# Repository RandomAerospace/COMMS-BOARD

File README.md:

Comms board with APRS GNSS
V1 has been flight tested, V2 has fixed existing issues under issues tab
Accompanying firmware: https://github.com/RandomAerospace/BEAR13_FIRMWARE
Summary of the project, presented at SARTS: https://www.sarts.org.sg/presentations-quarterly-meeting-may-2026/

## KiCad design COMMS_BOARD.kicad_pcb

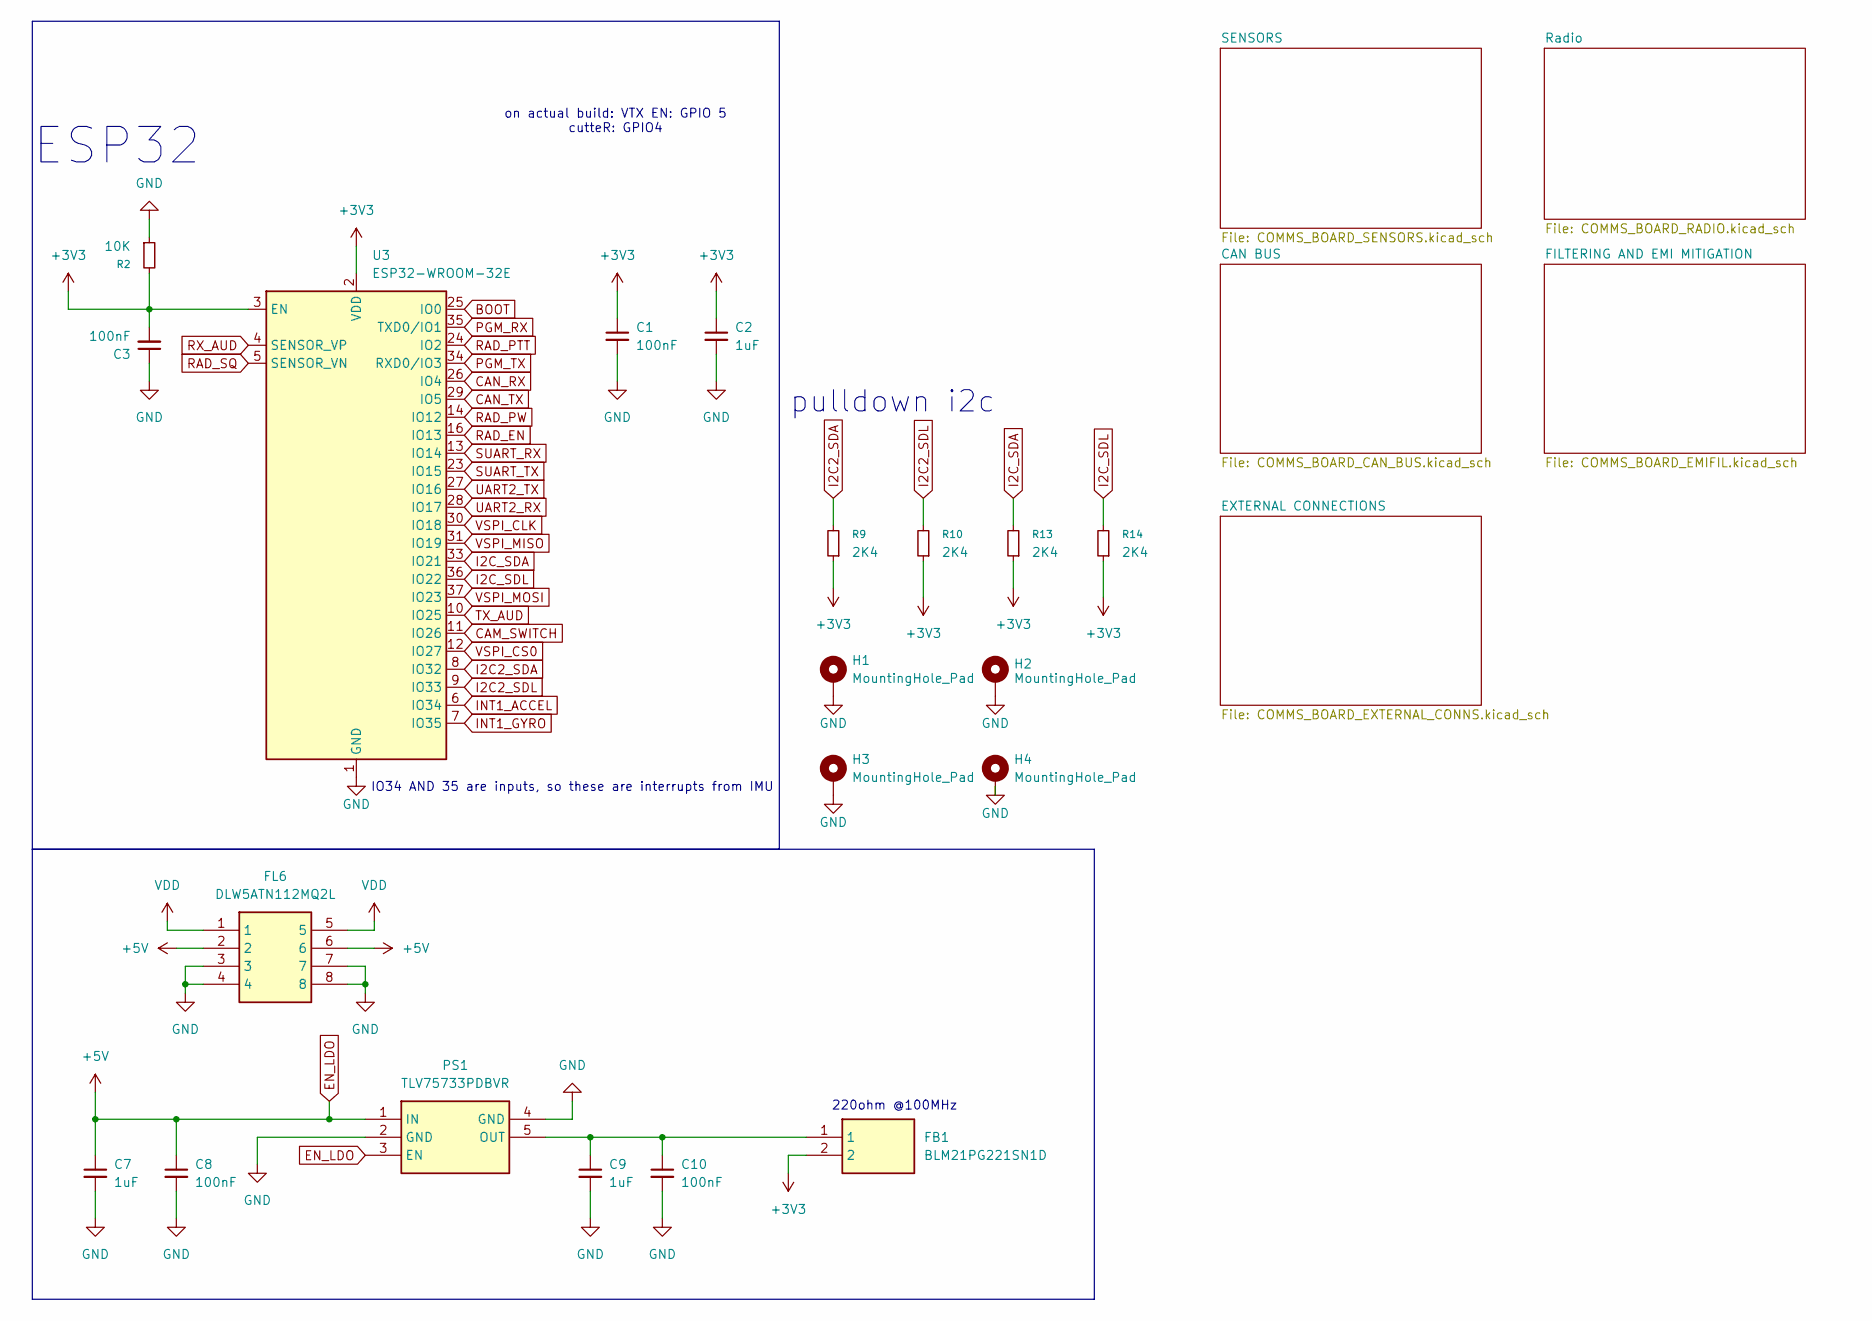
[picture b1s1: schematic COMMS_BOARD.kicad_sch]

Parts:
C1, C3, C8, C10: 100nF; C_0603_1608Metric
C2, C7, C9: 1uF; C_0603_1608Metric
FB1: BLM21PG221SN1D; BEADC2012X105N; Mouser Part Number 81-BLM21P221SG
FL6: DLW5ATN112MQ2L; DLW5BSN302SQ2L; Mouser Part Number 81-DLW5ATN112MQ2L
H1, H2, H3, H4: MountingHole_Pad; MountingHole_2.2mm_M2_ISO7380_Pad
PS1: TLV75733PDBVR; SOT95P280X145-5N; Mouser Part Number 595-TLV75733PDBVR
R2: 10K; R_0603_1608Metric
R9, R10, R13, R14: 2K4; R_0603_1608Metric
U3: ESP32-WROOM-32E; ESP32-WROOM-32D

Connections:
+3V3: C1.1, C2.1, C3.2, FB1.2, R2.2, R9.1, R10.1, R13.1, R14.1, U3.2 (VDD), U3.3 (EN); also elsewhere on the board
BOOT: U3.25 (IO0); also elsewhere on the board
CAM_SWITCH: U3.11 (IO26); also elsewhere on the board
CAN_RX: U3.26 (IO4); also elsewhere on the board
CAN_TX: U3.29 (IO5); also elsewhere on the board
EN_LDO: C7.1, C8.1, FL6.2, FL6.6, PS1.1 (IN), PS1.3 (EN); also elsewhere on the board
GND: C1.2, C2.2, C3.1, C7.2, C8.2, C9.2, C10.2, FL6.3, FL6.4, FL6.7, FL6.8, H1.1 (1_1), H2.1 (1_1), H3.1 (1_1), H4.1 (1_1), PS1.2 (GND), PS1.4 (GND), R2.1, U3.1 (GND), U3.15 (GND), U3.38 (GND), U3.39 (GND); also elsewhere on the board
I2C2_SDA: R9.2, U3.8 (IO32); also elsewhere on the board
I2C2_SDL: R10.2, U3.9 (IO33); also elsewhere on the board
I2C_SDA: R13.2, U3.33 (IO21); also elsewhere on the board
I2C_SDL: R14.2, U3.36 (IO22); also elsewhere on the board
INT1_ACCEL: U3.6 (IO34); also elsewhere on the board
INT1_GYRO: U3.7 (IO35); also elsewhere on the board
unnamed: FL6.1, FL6.5
unnamed: C9.1, C10.1, FB1.1, PS1.5 (OUT)
PGM_RX: U3.35 (TXD0/IO1); also elsewhere on the board
PGM_TX: U3.34 (RXD0/IO3); also elsewhere on the board
RAD_EN: U3.16 (IO13); also elsewhere on the board
RAD_PTT: U3.24 (IO2); also elsewhere on the board
RAD_PW: U3.14 (IO12); also elsewhere on the board
RAD_SQ: U3.5 (SENSOR_VN); also elsewhere on the board
RX_AUD: U3.4 (SENSOR_VP); also elsewhere on the board
SUART_RX: U3.13 (IO14); also elsewhere on the board
SUART_TX: U3.23 (IO15); also elsewhere on the board
TX_AUD: U3.10 (IO25); also elsewhere on the board
UART2_RX: U3.28 (IO17); also elsewhere on the board
UART2_TX: U3.27 (IO16); also elsewhere on the board
VSPI_CLK: U3.30 (IO18); also elsewhere on the board
VSPI_CS0: U3.12 (IO27); also elsewhere on the board
VSPI_MISO: U3.31 (IO19); also elsewhere on the board
VSPI_MOSI: U3.37 (IO23)

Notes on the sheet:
pulldown i2c
ESP32
IO34 AND 35 are inputs, so these are interrupts from IMU
220ohm @100MHz
on actual build: VTX EN: GPIO 5 cutteR: GPIO4

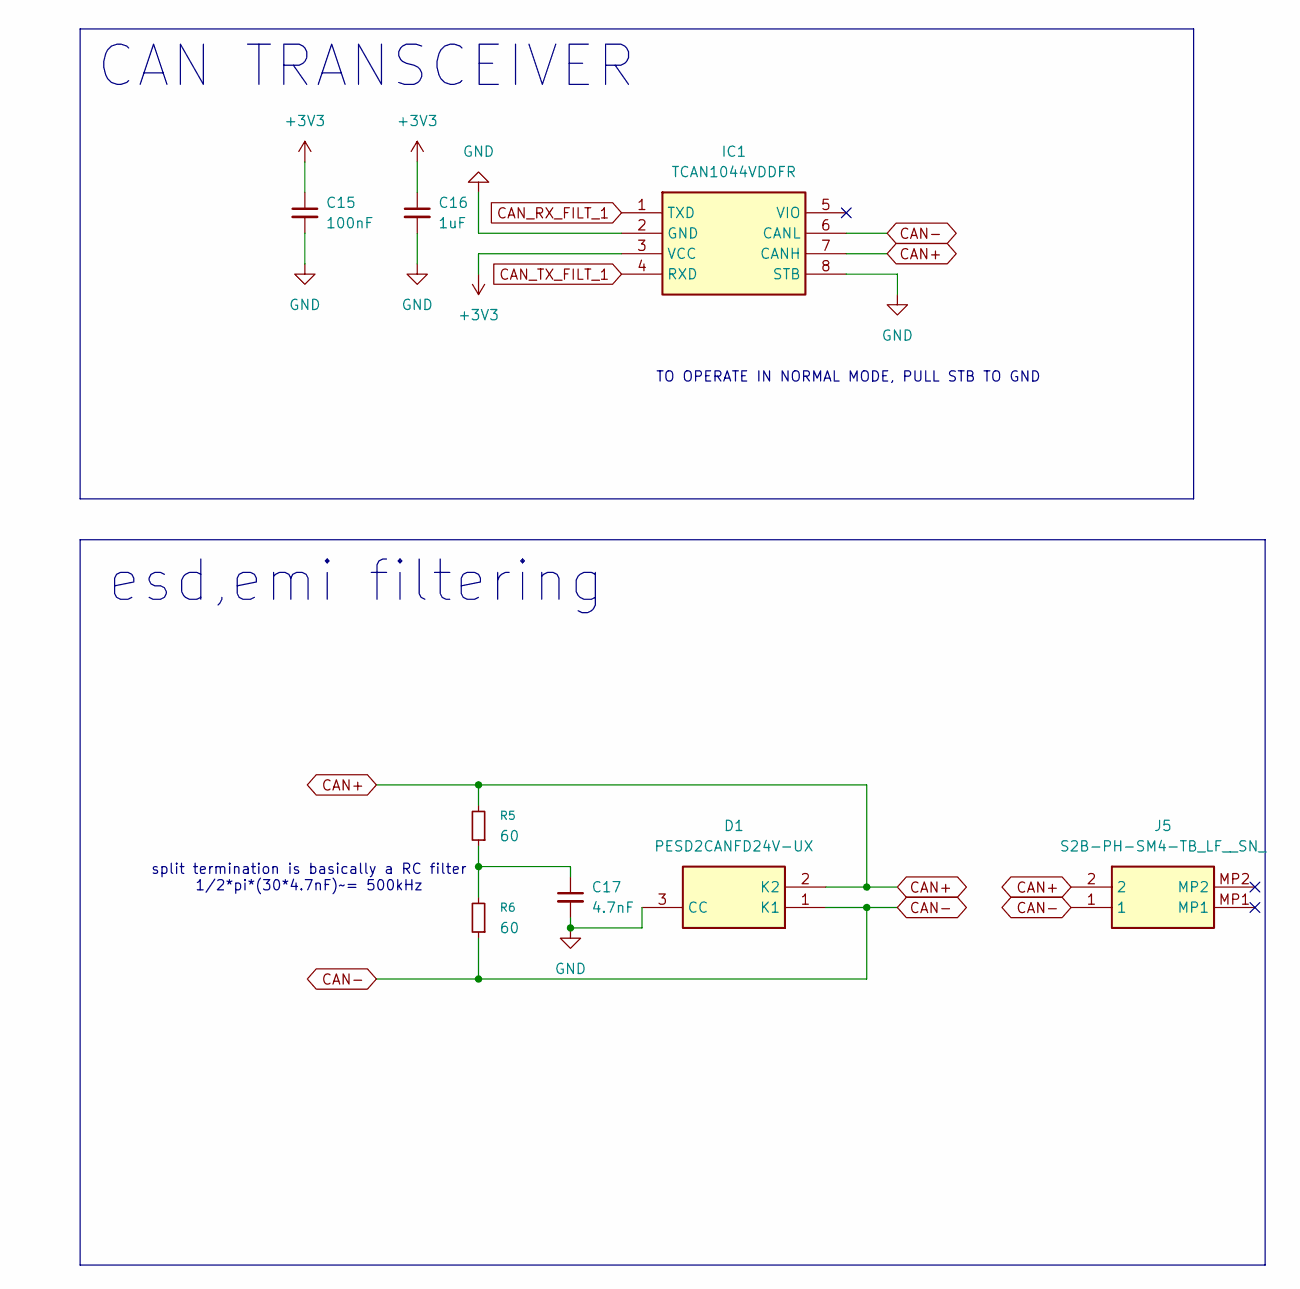
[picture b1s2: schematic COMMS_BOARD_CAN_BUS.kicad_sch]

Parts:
C15: 100nF; C_0603_1608Metric
C16: 1uF; C_0603_1608Metric
C17: 4.7nF; C_0603_1608Metric
D1: PESD2CANFD24V-UX; SOT65P210X110-3N; Mouser Part Number 771-PESD2CANFD24V-UX
IC1: TCAN1044VDDFR; SOT65P280X110-8N; Mouser Part Number 595-TCAN1044VDDFR
J5: S2B-PH-SM4-TB_LF__SN_; S2BPHSM4TBLFSN; Mouser Part Number N/A
R5, R6: 60; R_0603_1608Metric

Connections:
+3V3: C15.1, C16.1, IC1.3 (VCC); also elsewhere on the board
CAN+: D1.2 (K2), IC1.7 (CANH), J5.2, R5.2
CAN-: D1.1 (K1), IC1.6 (CANL), J5.1, R6.1
CAN_RX_FILT_1: IC1.1 (TXD); also elsewhere on the board
CAN_TX_FILT_1: IC1.4 (RXD); also elsewhere on the board
GND: C15.2, C16.2, C17.2, D1.3 (CC), IC1.2 (GND), IC1.8 (STB); also elsewhere on the board
unnamed: C17.1, R5.1, R6.2

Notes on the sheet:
split termination is basically a RC filter 1/2*pi*(30*4.7nF)~= 500kHz
esd,emi filtering
TO OPERATE IN NORMAL MODE, PULL STB TO GND
CAN TRANSCEIVER

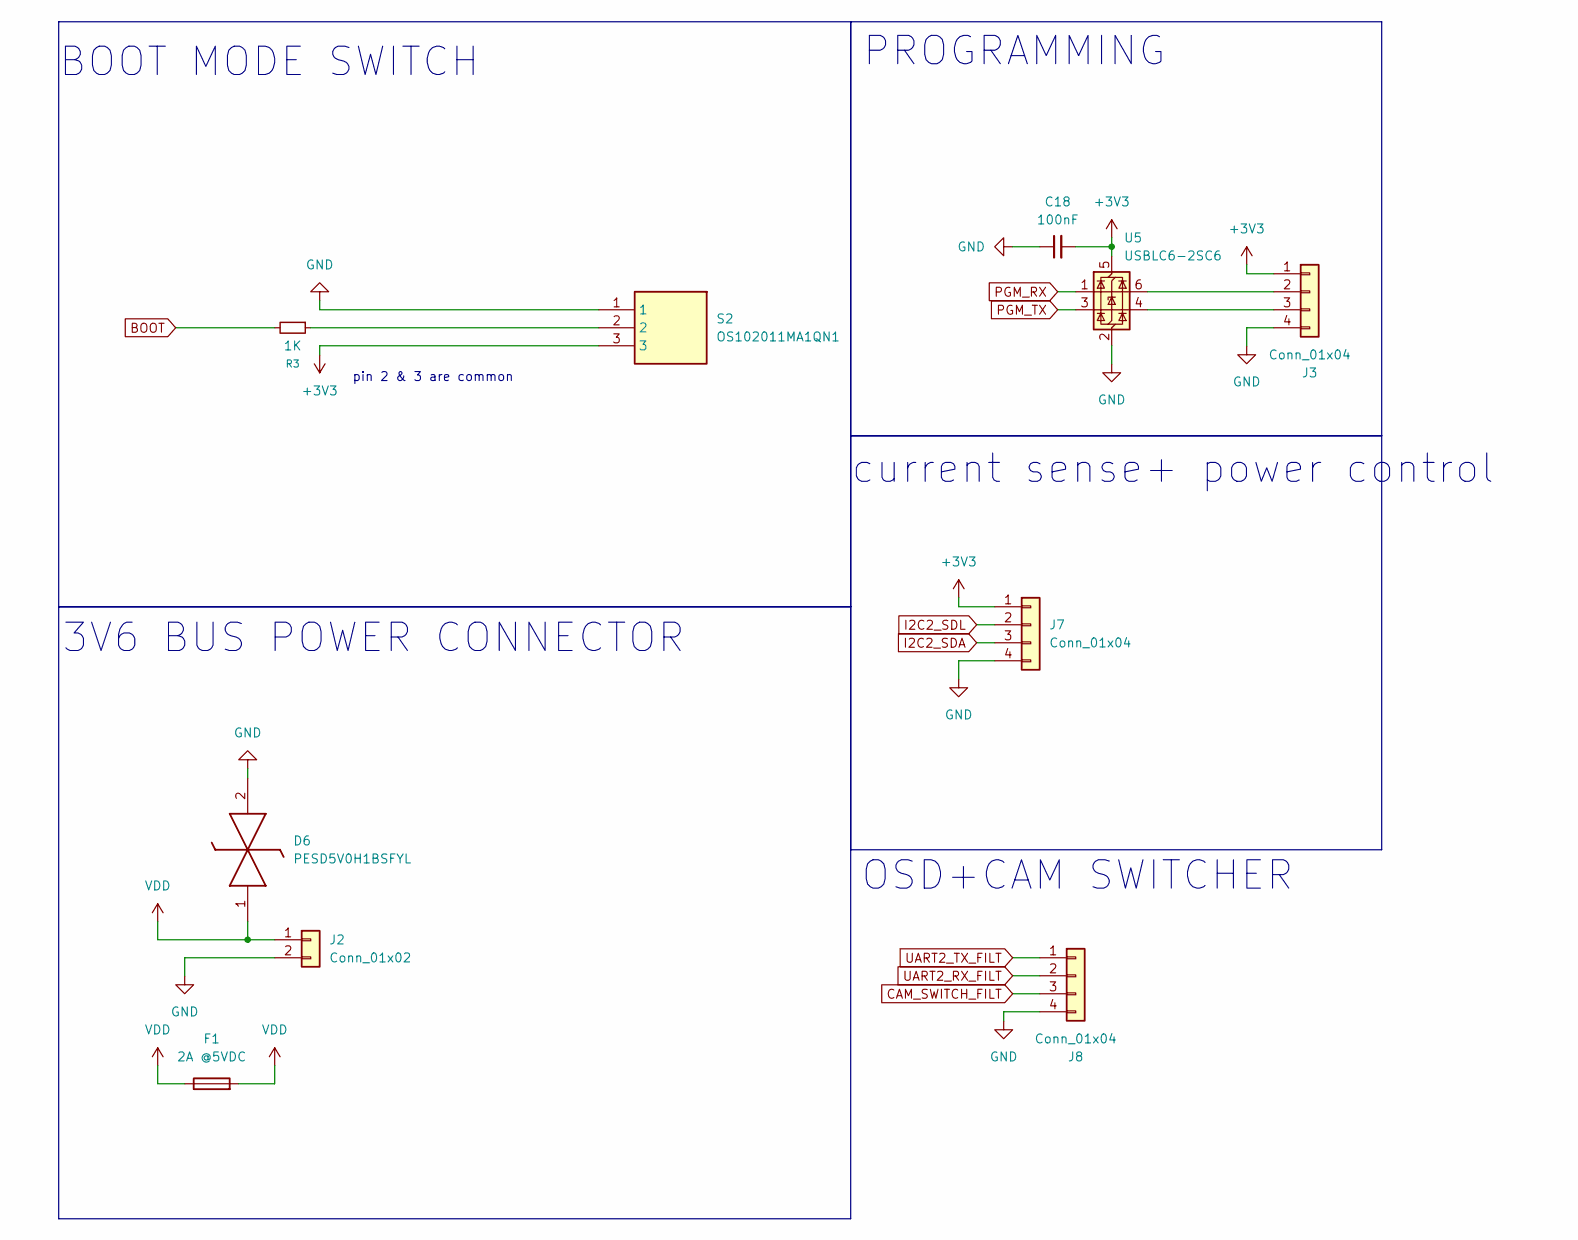
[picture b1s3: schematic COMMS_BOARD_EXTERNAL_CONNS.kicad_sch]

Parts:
C18: 100nF; C_0603_1608Metric
D6: PESD5V0H1BSFYL; PMEG3005AESFYL; Mouser Part Number 771-PESD5V0H1BSFYL
F1: 2A @5VDC; Fuse_0805_2012Metric
J2: Conn_01x02; JST_XH_S2B-XH-A-1_1x02_P2.50mm_Horizontal
J3, J8: Conn_01x04; JST_PH_B4B-PH-K_1x04_P2.00mm_Vertical
J7: Conn_01x04; JST_PH_S4B-PH-K_1x04_P2.00mm_Horizontal
R3: 1K; R_0603_1608Metric
S2: OS102011MA1QN1; Mouser Part Number 611-OS102011MA1QN1
U5: USBLC6-2SC6; SOT-23-6

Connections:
+3V3: C18.2, J3.1, J7.1, S2.3, U5.5 (VBUS); also elsewhere on the board
BOOT: R3.2; also elsewhere on the board
CAM_SWITCH_FILT: J8.3; also elsewhere on the board
GND: C18.1, D6.2 (K2), J2.2, J3.4, J7.4, J8.4, S2.1, U5.2 (GND); also elsewhere on the board
I2C2_SDA: J7.3; also elsewhere on the board
I2C2_SDL: J7.2; also elsewhere on the board
unnamed: J3.2, U5.6 (I/O1)
unnamed: J3.3, U5.4 (I/O2)
unnamed: R3.1, S2.2
PGM_RX: U5.1 (I/O1); also elsewhere on the board
PGM_TX: U5.3 (I/O2); also elsewhere on the board
UART2_RX_FILT: J8.2; also elsewhere on the board
UART2_TX_FILT: J8.1; also elsewhere on the board
VDD: D6.1 (K1), F1.1, F1.2, J2.1; also elsewhere on the board

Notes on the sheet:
PROGRAMMING
current sense+ power control
pin 2 & 3 are common
OSD+CAM SWITCHER
3V6 BUS POWER CONNECTOR
BOOT MODE SWITCH

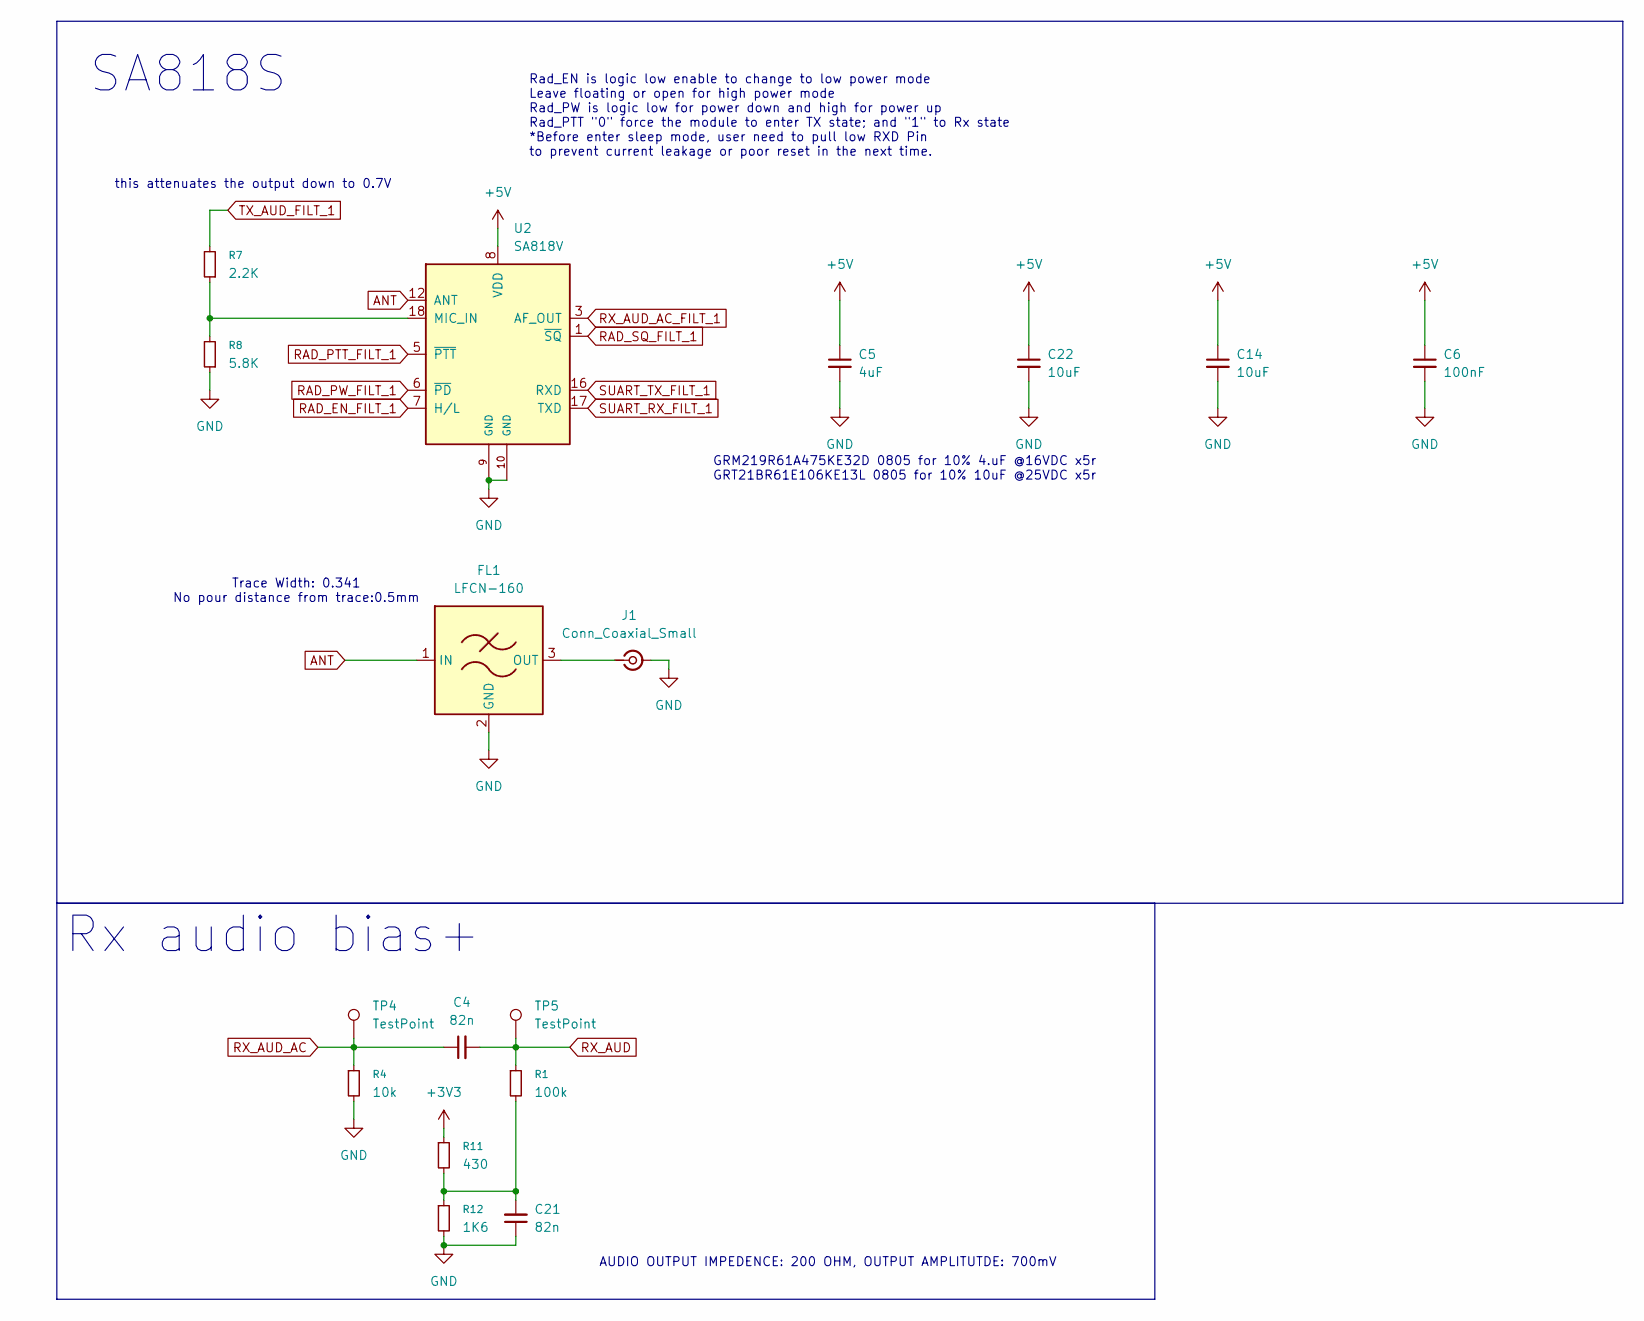
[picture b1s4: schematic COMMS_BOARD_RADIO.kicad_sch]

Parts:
C4, C21: 82n; C_0603_1608Metric
C5: 4uF; C_0805_2012Metric
C6: 100nF; C_0603_1608Metric
C14, C22: 10uF; C_0805_2012Metric
FL1: LFCN-160; Filter_Mini-Circuits_FV1206
J1: Conn_Coaxial_Small; MMCX_Molex_73415-1471_Vertical
R1: 100k; R_0603_1608Metric
R4: 10k; R_0603_1608Metric
R7: 2.2K; R_0603_1608Metric
R8: 5.8K; R_0603_1608Metric
R11: 430; R_0603_1608Metric
R12: 1K6; R_0603_1608Metric
TP4, TP5: TestPoint; TestPoint_Pad_D1.5mm
U2: SA818V; VHF_UHF_Module_generic

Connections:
+3V3: R11.1; also elsewhere on the board
ANT: FL1.1 (IN), U2.12 (ANT)
EN_LDO: C5.1, C6.1, C14.1, C22.1, U2.8 (VDD); also elsewhere on the board
GND: C5.2, C6.2, C14.2, C21.1, C22.2, FL1.2 (GND), FL1.4 (GND), J1.2 (Ext), R4.2, R8.1, R12.2, U2.9 (GND), U2.10 (GND); also elsewhere on the board
unnamed: C21.2, R1.2, R11.2, R12.1
unnamed: FL1.3 (OUT), J1.1 (In)
unnamed: R7.1, R8.2, U2.18 (MIC_IN)
RAD_EN_FILT_1: U2.7 (H/L); also elsewhere on the board
RAD_PTT_FILT_1: U2.5 (~PTT); also elsewhere on the board
RAD_PW_FILT_1: U2.6 (~PD); also elsewhere on the board
RAD_SQ_FILT_1: U2.1 (~SQ); also elsewhere on the board
RX_AUD: C4.2, R1.1, TP5.1 (1_1); also elsewhere on the board
RX_AUD_AC: C4.1, R4.1, TP4.1 (1_1); also elsewhere on the board
RX_AUD_AC_FILT_1: U2.3 (AF_OUT); also elsewhere on the board
SUART_RX_FILT_1: U2.17 (TXD); also elsewhere on the board
SUART_TX_FILT_1: U2.16 (RXD); also elsewhere on the board
TX_AUD_FILT_1: R7.2; also elsewhere on the board

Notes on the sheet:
SA818S
Trace Width: 0.341 No pour distance from trace:0.5mm
Rad_EN is logic low enable to change to low power mode Leave floating or open for high power mode Rad_PW is logic low for power down and high for power up Rad_PTT "0" force the module to enter TX state; and "1" to Rx state *Before enter sleep mode, user need to pull low RXD Pin to prevent current l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
this attenuates the output down to 0.7V
GRM219R61A475KE32D 0805 for 10% 4.uF @16VDC x5r GRT21BR61E106KE13L 0805 for 10% 10uF @25VDC x5r
Rx audio bias+
AUDIO OUTPUT IMPEDENCE: 200 OHM, OUTPUT AMPLITUTDE: 700mV

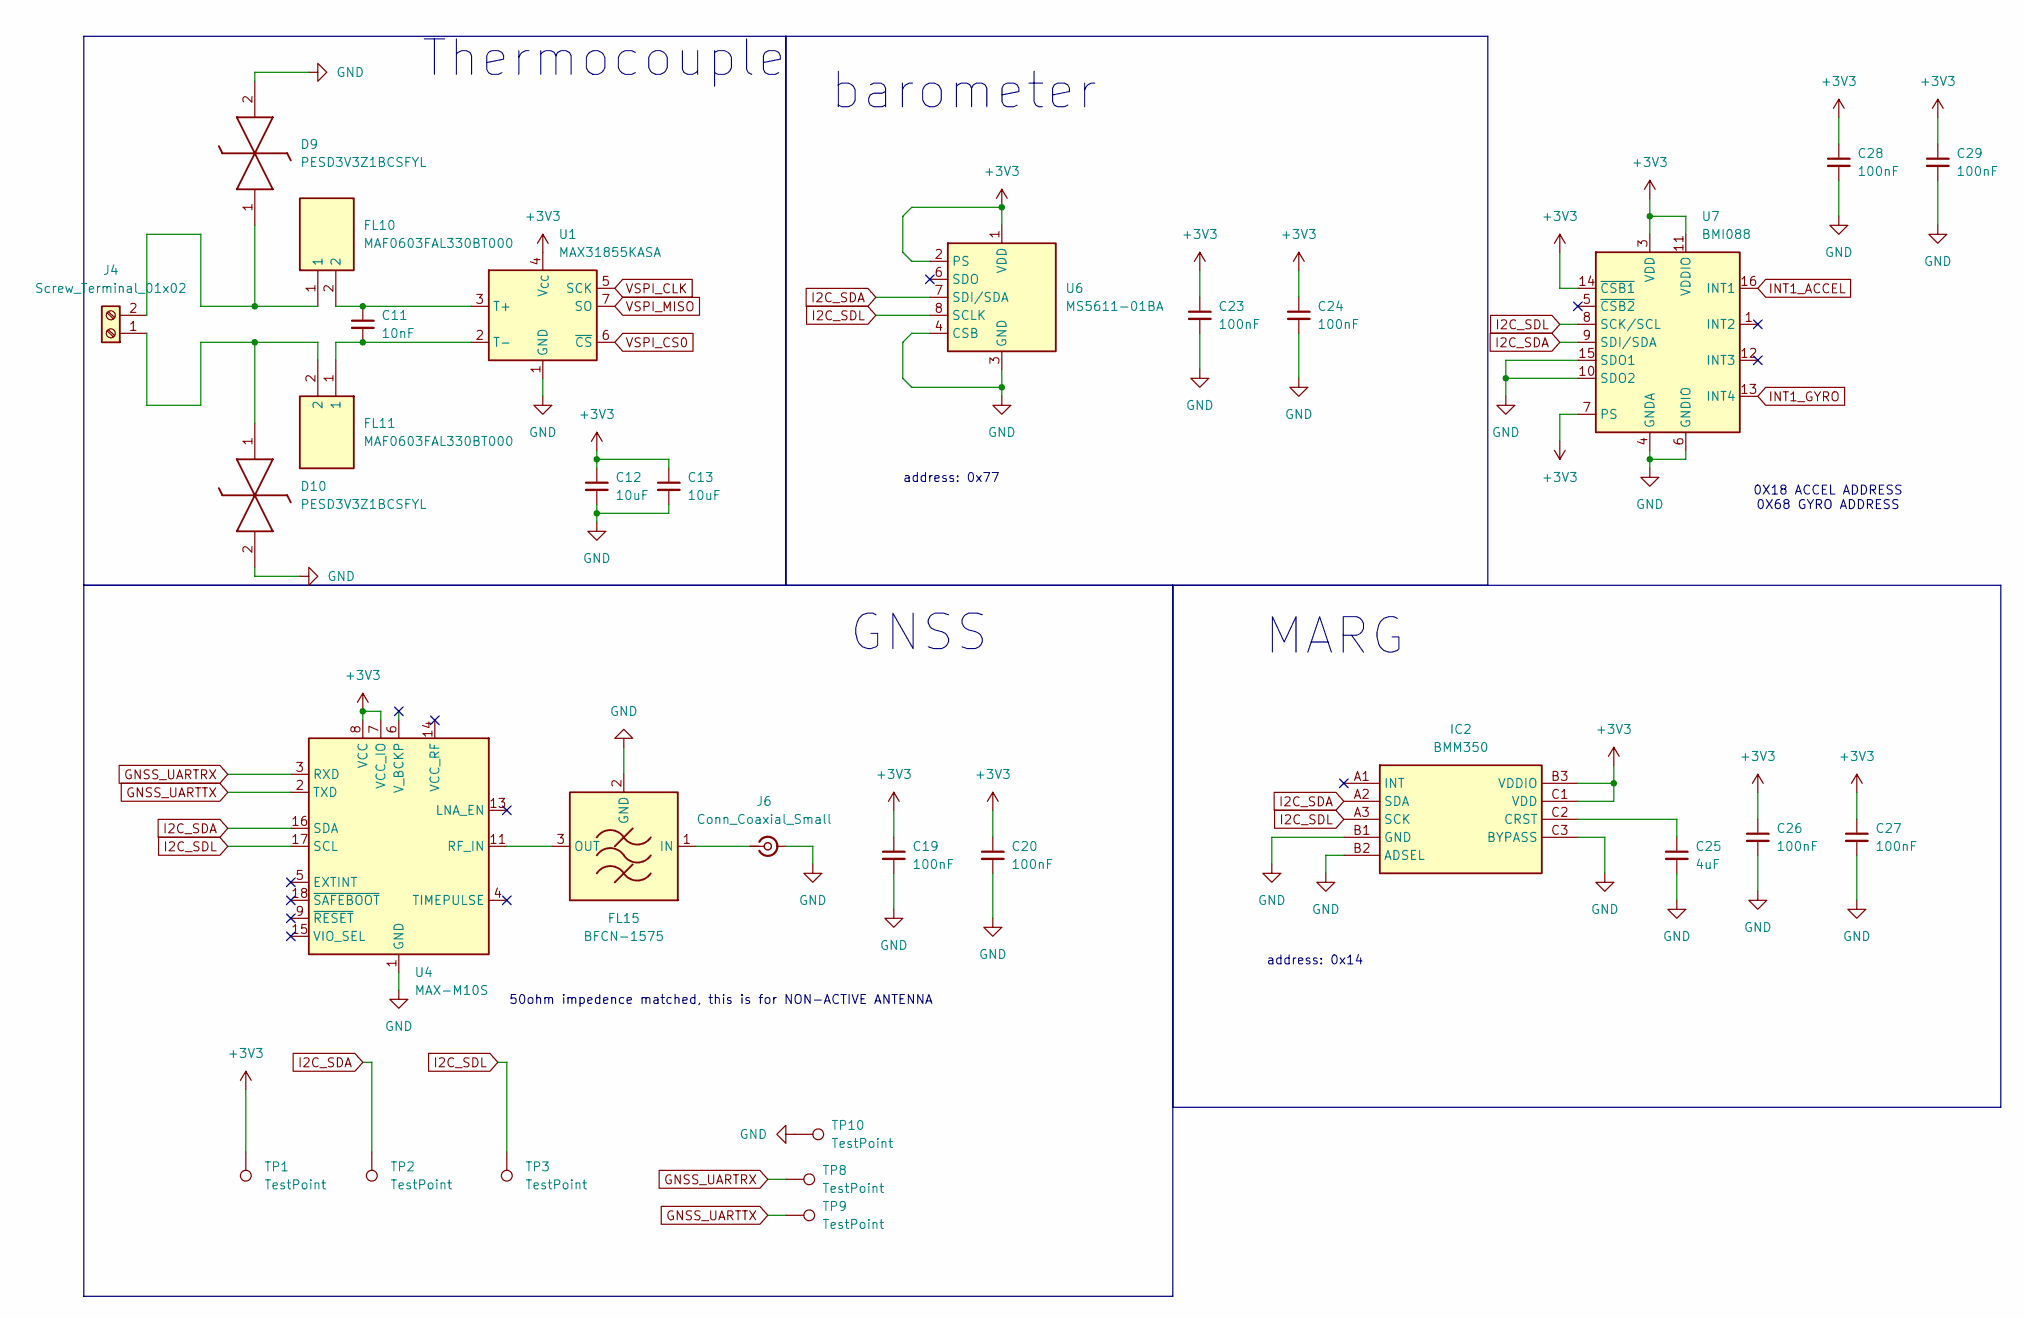
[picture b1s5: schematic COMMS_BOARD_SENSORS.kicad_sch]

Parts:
C11: 10nF; C_0603_1608Metric
C12, C13: 10uF; C_0603_1608Metric
C19, C20, C23, C24, C26, C27, C28, C29: 100nF; C_0603_1608Metric
C25: 4uF; C_0805_2012Metric
D9, D10: PESD3V3Z1BCSFYL; PMEG3005AESFYL; Mouser Part Number 771-PESD3V3Z1BCSFYL
FL10, FL11: MAF0603FAL330BT000; BEADC0603X33N; Mouser Part Number 810-MAF0603FAL330BT0
FL15: BFCN-1575; Filter_Mini-Circuits_FV1206
IC2: BMM350; BGA9C40P3X3_128X128X54; Mouser Part Number 262-BMM350
J4: Screw_Terminal_01x02; TerminalBlock_Xinya_XY308-2.54-2P_1x02_P2.54mm_Horizontal
J6: Conn_Coaxial_Small; U.FL_Hirose_U.FL-R-SMT-1_Vertical
TP1, TP2, TP3, TP8, TP9, TP10: TestPoint; TestPoint_Pad_D1.5mm
U1: MAX31855KASA; SOIC-8_3.9x4.9mm_P1.27mm
U4: MAX-M10S; ublox_MAX
U6: MS5611-01BA; LGA-8_3x5mm_P1.25mm
U7: BMI088; Bosch_LGA-16_4.5x3mm_P0.5mm_LayoutBorder7x1y_ClockwisePinNu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

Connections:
+3V3: C12.1, C13.1, C19.1, C20.1, C23.1, C24.1, C26.1, C27.1, C28.1, C29.1, IC2.B3 (VDDIO), IC2.C1 (VDD), TP1.1 (1_1), U1.4 (V_{CC}), U4.7 (VCC_IO), U4.8 (VCC), U6.1 (VDD), U6.2 (PS), U7.3 (VDD), U7.7 (PS), U7.11 (VDDIO), U7.14 (~CSB1); also elsewhere on the board
GND: C12.2, C13.2, C19.2, C20.2, C23.2, C24.2, C25.2, C26.2, C27.2, C28.2, C29.2, D9.2 (K2), D10.2 (K2), FL15.2 (GND), FL15.4 (GND), IC2.B1 (GND), IC2.B2 (ADSEL), IC2.C3 (BYPASS), J6.2 (Ext), TP10.1 (1_1), U1.1 (GND), U4.1 (GND), U4.10 (GND), U4.12 (GND), U6.3 (GND), U6.4 (CSB), U6.5 (CSB), U7.2 (GNDA), U7.4 (GNDA), U7.6 (GNDIO), U7.10 (SDO2), U7.15 (SDO1); also elsewhere on the board
GNSS_UARTRX: TP8.1 (1_1), U4.3 (RXD); also elsewhere on the board
GNSS_UARTTX: TP9.1 (1_1), U4.2 (TXD); also elsewhere on the board
I2C_SDA: IC2.A2 (SDA), TP2.1 (1_1), U4.16 (SDA), U6.7 (SDI/SDA), U7.9 (SDI/SDA); also elsewhere on the board
I2C_SDL: IC2.A3 (SCK), TP3.1 (1_1), U4.17 (SCL), U6.8 (SCLK), U7.8 (SCK/SCL); also elsewhere on the board
INT1_ACCEL: U7.16 (INT1); also elsewhere on the board
INT1_GYRO: U7.13 (INT4); also elsewhere on the board
unnamed: D9.1 (K1), FL10.1, J4.2
unnamed: D10.1 (K1), FL11.2, J4.1
unnamed: FL15.1 (IN), J6.1 (In)
unnamed 30: FL15.3 (OUT), U4.11 (RF_IN); also elsewhere on the board
unnamed: C25.1, IC2.C2 (CRST)
unnamed: C11.1, FL10.2, U1.3 (T+)
unnamed: C11.2, FL11.1, U1.2 (T-)
VSPI_CLK: U1.5 (SCK); also elsewhere on the board
VSPI_CS0: U1.6 (~CS); also elsewhere on the board
VSPI_MISO: U1.7 (SO); also elsewhere on the board

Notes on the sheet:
0X18 ACCEL ADDRESS 0X68 GYRO ADDRESS
address: 0x14
barometer
address: 0x77
GNSS
MARG
Thermocouple
50ohm impedence matched, this is for NON-ACTIVE ANTENNA

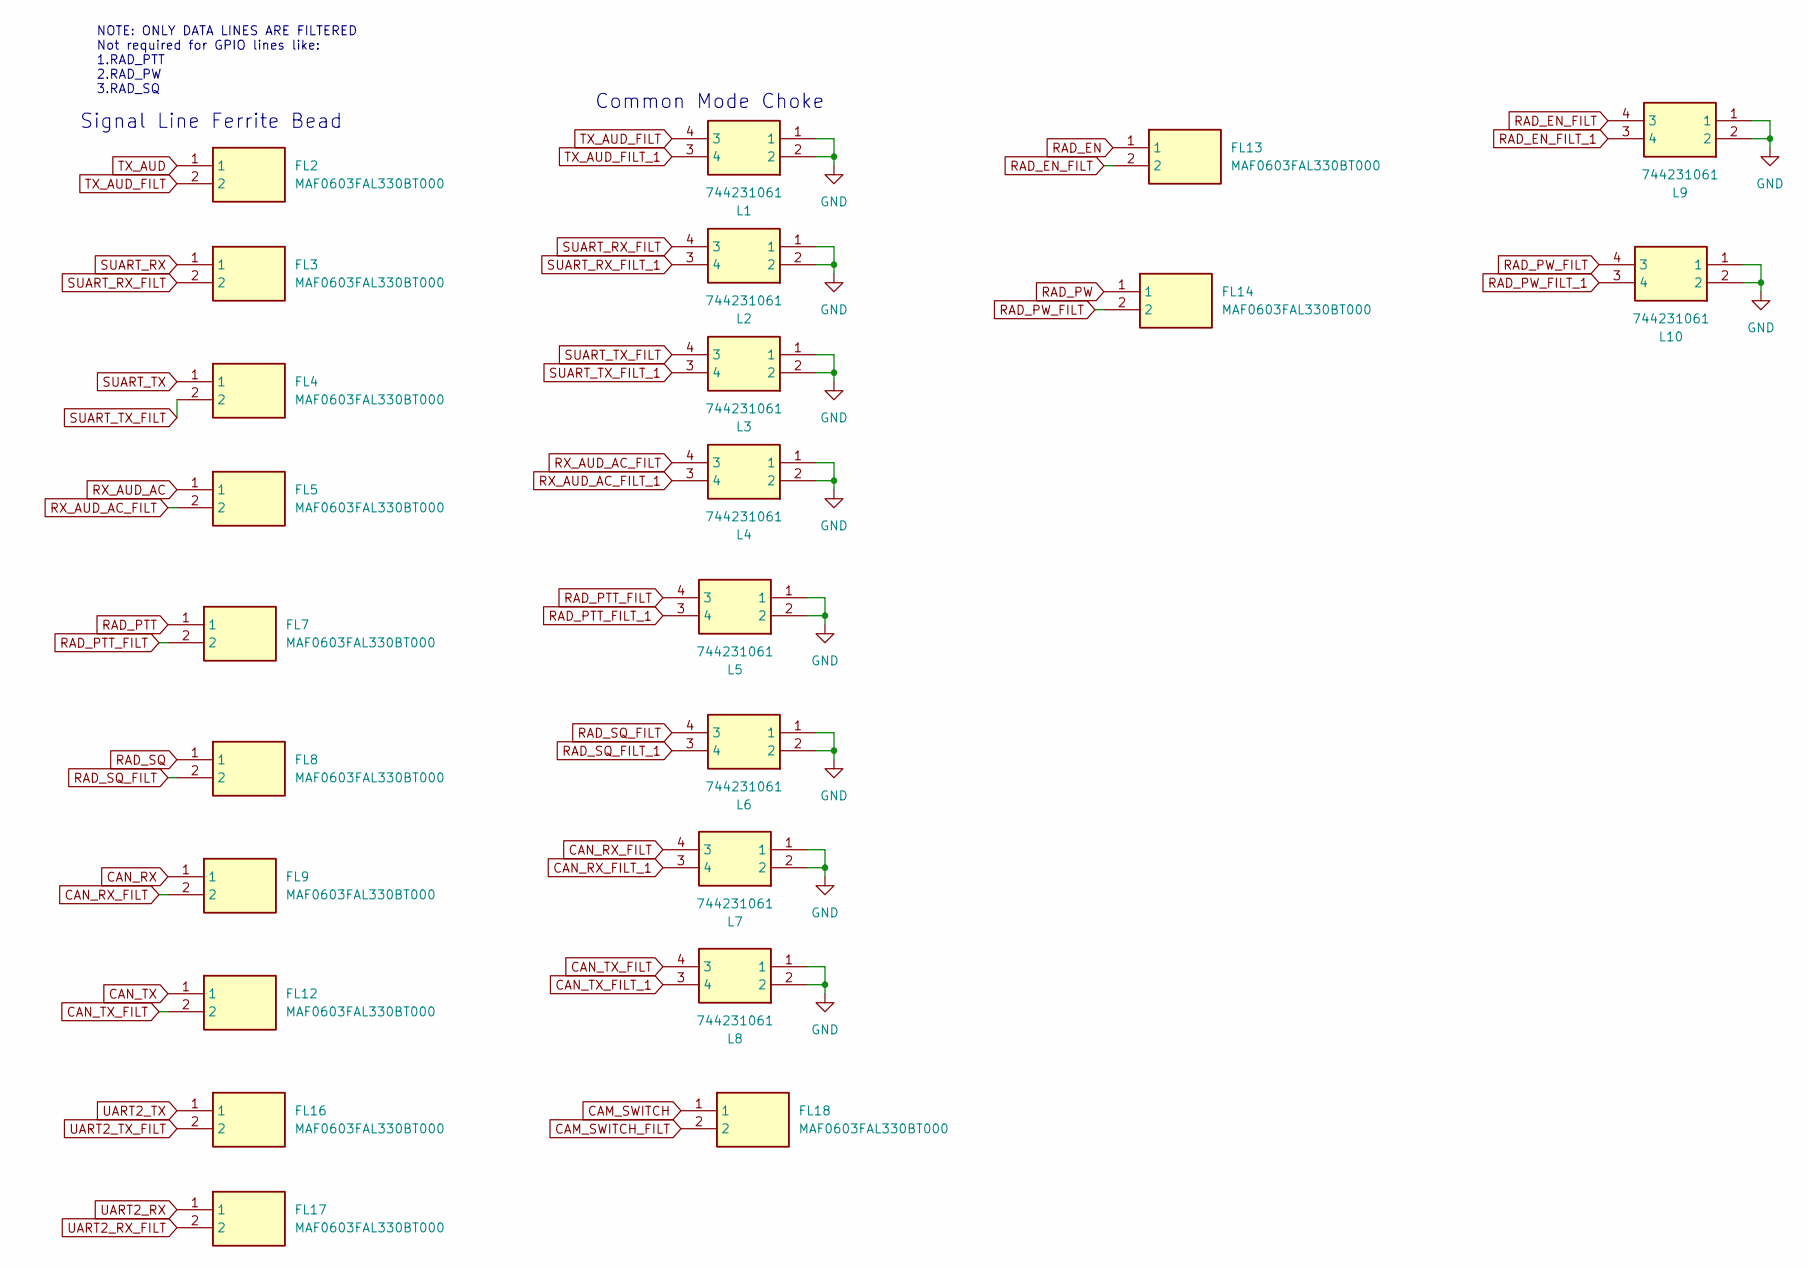
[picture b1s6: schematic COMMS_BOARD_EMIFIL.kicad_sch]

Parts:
FL2, FL3, FL4, FL5, FL7, FL8, FL9, FL12, FL13, FL14, FL16, FL17, FL18: MAF0603FAL330BT000; BEADC0603X33N; Mouser Part Number 810-MAF0603FAL330BT0
L1, L2, L3, L4, L5, L6, L7, L8, L9, L10: 744231061; WE-CNSW_08058; Mouser Part Number 710-744231061

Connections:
CAM_SWITCH: FL18.1; also elsewhere on the board
CAM_SWITCH_FILT: FL18.2; also elsewhere on the board
CAN_RX: FL9.1; also elsewhere on the board
CAN_RX_FILT: FL9.2, L7.4 (3)
CAN_RX_FILT_1: L7.3 (4); also elsewhere on the board
CAN_TX: FL12.1; also elsewhere on the board
CAN_TX_FILT: FL12.2, L8.4 (3)
CAN_TX_FILT_1: L8.3 (4); also elsewhere on the board
GND: L1.1, L1.2, L2.1, L2.2, L3.1, L3.2, L4.1, L4.2, L5.1, L5.2, L6.1, L6.2, L7.1, L7.2, L8.1, L8.2, L9.1, L9.2, L10.1, L10.2; also elsewhere on the board
RAD_EN: FL13.1; also elsewhere on the board
RAD_EN_FILT: FL13.2, L9.4 (3)
RAD_EN_FILT_1: L9.3 (4); also elsewhere on the board
RAD_PTT: FL7.1; also elsewhere on the board
RAD_PTT_FILT: FL7.2, L5.4 (3)
RAD_PTT_FILT_1: L5.3 (4); also elsewhere on the board
RAD_PW: FL14.1; also elsewhere on the board
RAD_PW_FILT: FL14.2, L10.4 (3)
RAD_PW_FILT_1: L10.3 (4); also elsewhere on the board
RAD_SQ: FL8.1; also elsewhere on the board
RAD_SQ_FILT: FL8.2, L6.4 (3)
RAD_SQ_FILT_1: L6.3 (4); also elsewhere on the board
RX_AUD_AC: FL5.1; also elsewhere on the board
RX_AUD_AC_FILT: FL5.2, L4.4 (3)
RX_AUD_AC_FILT_1: L4.3 (4); also elsewhere on the board
SUART_RX: FL3.1; also elsewhere on the board
SUART_RX_FILT: FL3.2, L2.4 (3)
SUART_RX_FILT_1: L2.3 (4); also elsewhere on the board
SUART_TX: FL4.1; also elsewhere on the board
SUART_TX_FILT: FL4.2, L3.4 (3)
SUART_TX_FILT_1: L3.3 (4); also elsewhere on the board
TX_AUD: FL2.1; also elsewhere on the board
TX_AUD_FILT: FL2.2, L1.4 (3)
TX_AUD_FILT_1: L1.3 (4); also elsewhere on the board
UART2_RX: FL17.1; also elsewhere on the board
UART2_RX_FILT: FL17.2; also elsewhere on the board
UART2_TX: FL16.1; also elsewhere on the board
UART2_TX_FILT: FL16.2; also elsewhere on the board

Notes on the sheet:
Signal Line Ferrite Bead
NOTE: ONLY DATA LINES ARE FILTERED Not required for GPIO lines like: 1.RAD_PTT 2.RAD_PW 3.RAD_SQ
Common Mode Choke
